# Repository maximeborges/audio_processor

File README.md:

# Audio processor

- Symbols: https://github.com/maximeborges/kicad-symbols
- Footprints: https://github.com/maximeborges/kicad-footprints-v4

## Internet sharing to PYNQ via Ethernet

From https://wiki.archlinux.org/index.php/Internet_sharing

### On the PYNQ:
  
    ip route add default via 192.168.2.1 dev eth0

Where `192.168.2.1` is the computer sharing the connexion.

### On the other computer:

Replace `net0` with local network and `internet0` with external network. For example `net0`->`enp9s0` and `internet0`->`wlp8s0`.

    sysctl net.ipv4.ip_forward=1
    iptables -t nat -A POSTROUTING -o internet0 -j MASQUERADE
    iptables -A FORWARD -m conntrack --ctstate RELATED,ESTABLISHED -j ACCEPT
    iptables -A FORWARD -i net0 -o internet0 -j ACCEPT

### DNS resolution:
Add to /etc/resolv.conf:

    nameserver 185.121.177.177
    nameserver 185.121.177.53

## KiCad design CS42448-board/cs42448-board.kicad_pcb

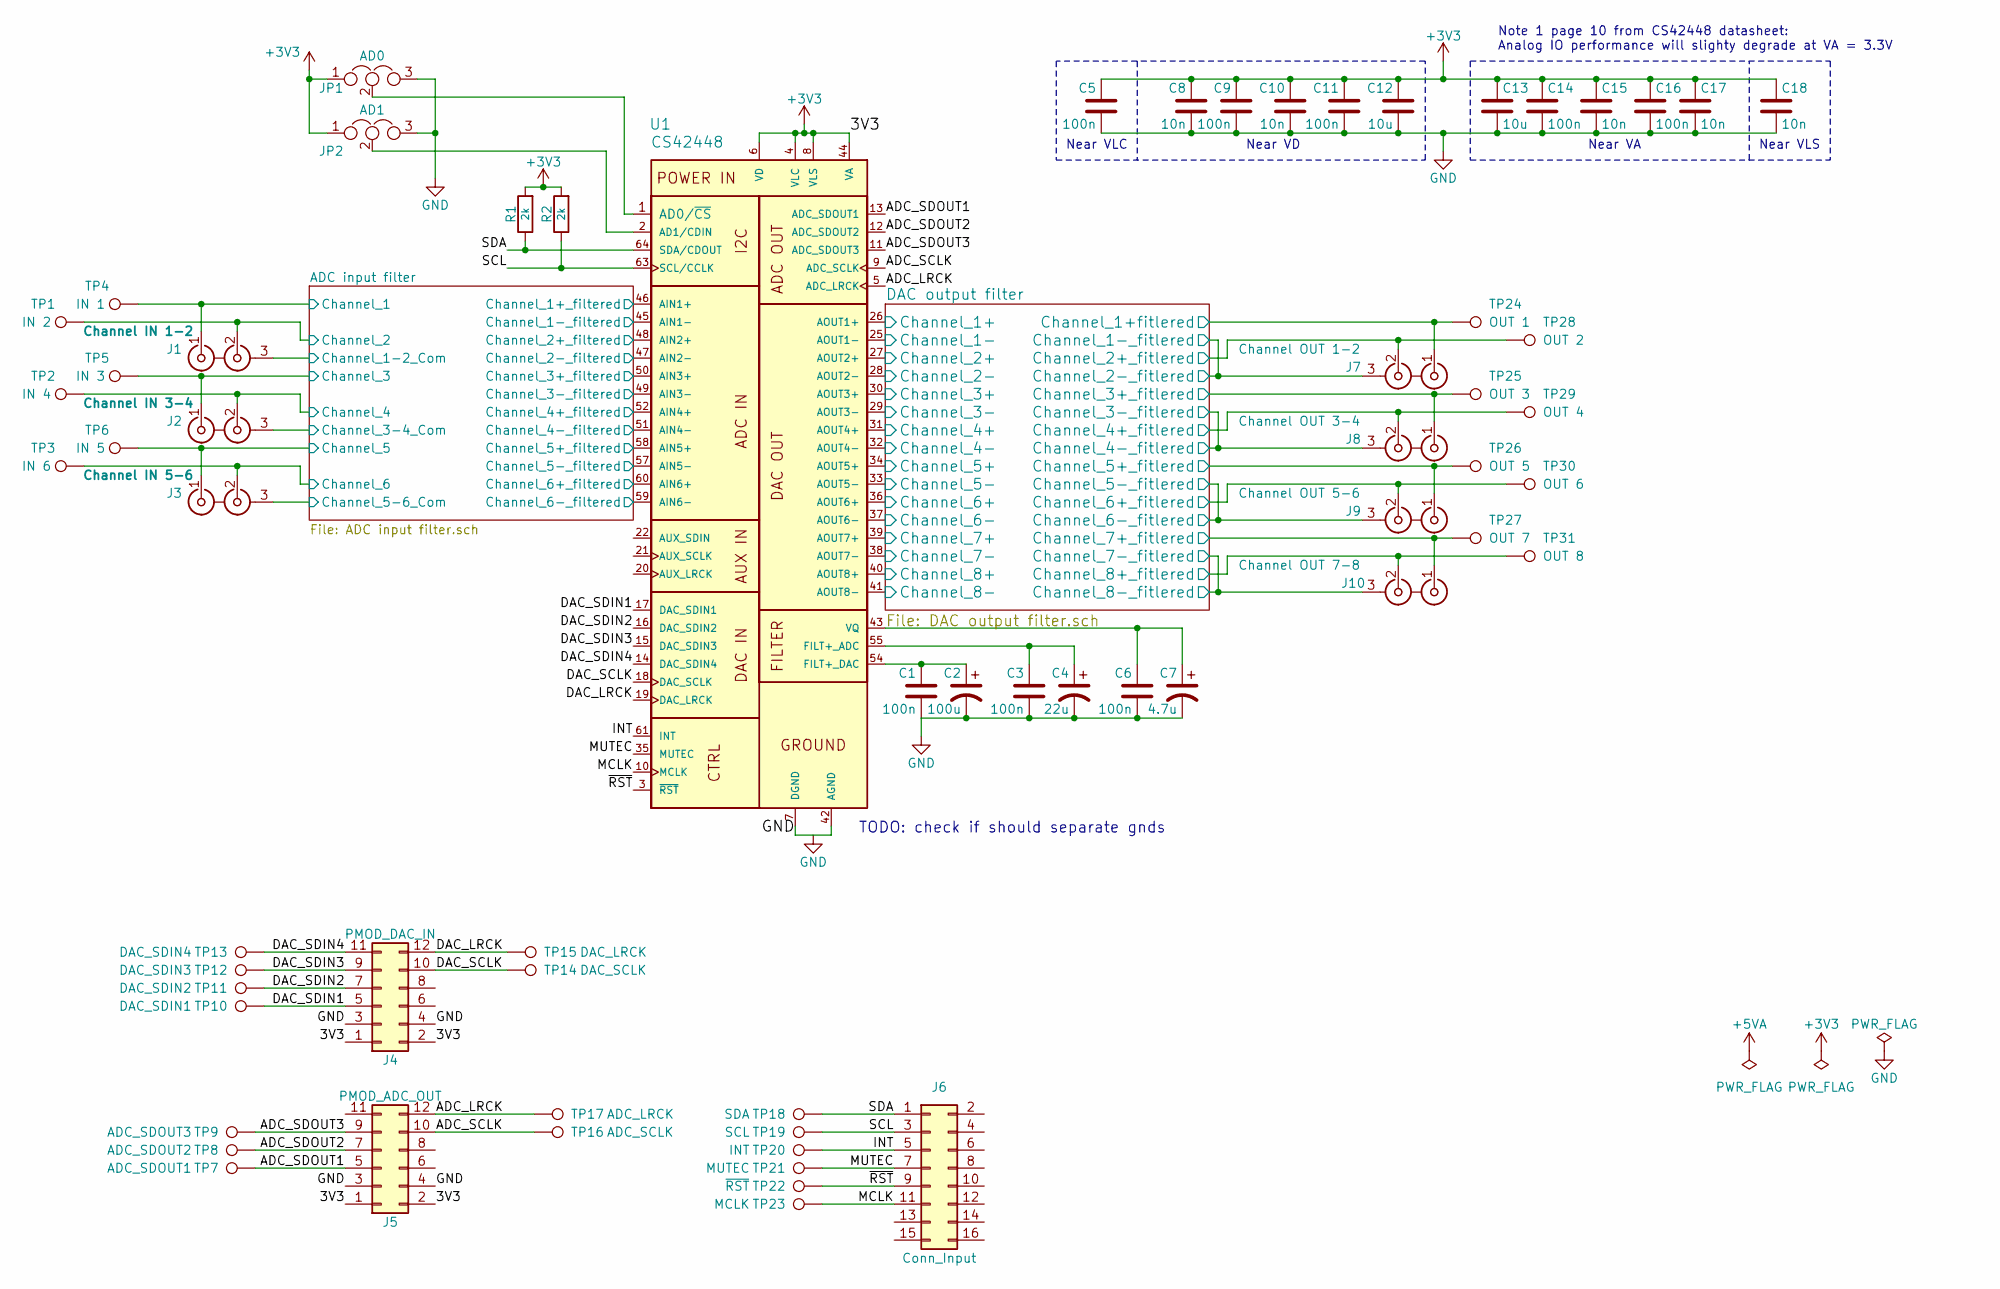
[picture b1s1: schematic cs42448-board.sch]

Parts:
C1, C3, C5, C6, C9, C11, C14, C16: 100n; C_1206_HandSoldering
C2: 100u; CP_Radial_D5.0mm_P2.00mm
C4: 22u; CP_Radial_D5.0mm_P2.00mm
C7: 4.7u; CP_Radial_D5.0mm_P2.00mm
C8, C10, C15, C17, C18: 10n; C_1206_HandSoldering
C12, C13: 10u; C_1206_HandSoldering
J1: Channel IN 1-2; PJRAS1X2S01AUX
J2: Channel IN 3-4; PJRAS1X2S01AUX
J3: Channel IN 5-6; PJRAS1X2S01AUX
J4: PMOD_DAC_IN; PinHeader_2x06_P2.54mm_Horizontal
J5: PMOD_ADC_OUT; PinHeader_2x06_P2.54mm_Horizontal
J6: Conn_Input; Pin_Header_Straight_2x08_Pitch2.54mm
J7: Channel OUT 1-2; PJRAS1X2S01AUX
J8: Channel OUT 3-4; PJRAS1X2S01AUX
J9: Channel OUT 5-6; PJRAS1X2S01AUX
J10: Channel OUT 7-8; PJRAS1X2S01AUX
JP1: AD0; SolderJumper-3_P1.3mm_Open_Pad1.0x1.5mm
JP2: AD1; SolderJumper-3_P1.3mm_Open_Pad1.0x1.5mm
R1, R2: 2k; R_1206_HandSoldering
TP1: IN 2; PINTST
TP2: IN 4; PINTST
TP3: IN 6; PINTST
TP4: IN 1; PINTST
TP5: IN 3; PINTST
TP6: IN 5; PINTST
TP7: ADC_SDOUT1; PINTST
TP8: ADC_SDOUT2; PINTST
TP9: ADC_SDOUT3; PINTST
TP10: DAC_SDIN1; PINTST
TP11: DAC_SDIN2; PINTST
TP12: DAC_SDIN3; PINTST
TP13: DAC_SDIN4; PINTST
TP14: DAC_SCLK; PINTST
TP15: DAC_LRCK; PINTST
TP16: ADC_SCLK; PINTST
TP17: ADC_LRCK; PINTST
TP18: SDA; PINTST
TP19: SCL; PINTST
TP20: INT; PINTST
TP21: MUTEC; PINTST
TP22: ~RST; PINTST
TP23: MCLK; PINTST
TP24: OUT 1; PINTST
TP25: OUT 3; PINTST
TP26: OUT 5; PINTST
TP27: OUT 7; PINTST
TP28: OUT 2; PINTST
TP29: OUT 4; PINTST
TP30: OUT 6; PINTST
TP31: OUT 8; PINTST
U1: CS42448; LQFP-64_10x10mm_P0.5mm

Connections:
+3V3: C5.1, C8.1, C9.1, C10.1, C11.1, C12.1, C13.1, C14.1, C15.1, C16.1, C17.1, C18.1, J4.1, J4.2, J5.1, J5.2, JP1.1, JP2.1, R1.2, R2.2, U1.4 (VLC), U1.6 (VD), U1.8 (VLS), U1.24 (VD), U1.44 (VA), U1.53 (VA)
/ADC input filter/Channel_1: J1.1 (IN1), TP4.1; also elsewhere on the board
/ADC input filter/Channel_1+_filtered: U1.46 (AIN1+); also elsewhere on the board
/ADC input filter/Channel_1-2_Com: J1.3 (EXT); also elsewhere on the board
/ADC input filter/Channel_1-_filtered: U1.45 (AIN1-); also elsewhere on the board
/ADC input filter/Channel_2: J1.2 (IN2), TP1.1; also elsewhere on the board
/ADC input filter/Channel_2+_filtered: U1.48 (AIN2+); also elsewhere on the board
/ADC input filter/Channel_2-_filtered: U1.47 (AIN2-); also elsewhere on the board
/ADC input filter/Channel_3: J2.1 (IN1), TP5.1; also elsewhere on the board
/ADC input filter/Channel_3+_filtered: U1.50 (AIN3+); also elsewhere on the board
/ADC input filter/Channel_3-4_Com: J2.3 (EXT); also elsewhere on the board
/ADC input filter/Channel_3-_filtered: U1.49 (AIN3-); also elsewhere on the board
/ADC input filter/Channel_4: J2.2 (IN2), TP2.1; also elsewhere on the board
/ADC input filter/Channel_4+_filtered: U1.52 (AIN4+); also elsewhere on the board
/ADC input filter/Channel_4-_filtered: U1.51 (AIN4-); also elsewhere on the board
/ADC input filter/Channel_5: J3.1 (IN1), TP6.1; also elsewhere on the board
/ADC input filter/Channel_5+_filtered: U1.58 (AIN5+); also elsewhere on the board
/ADC input filter/Channel_5-6_Com: J3.3 (EXT); also elsewhere on the board
/ADC input filter/Channel_5-_filtered: U1.57 (AIN5-); also elsewhere on the board
/ADC input filter/Channel_6: J3.2 (IN2), TP3.1; also elsewhere on the board
/ADC input filter/Channel_6+_filtered: U1.60 (AIN6+); also elsewhere on the board
/ADC input filter/Channel_6-_filtered: U1.59 (AIN6-); also elsewhere on the board
/ADC_LRCK: J5.12, TP17.1, U1.5 (ADC_LRCK)
/ADC_SCLK: J5.10, TP16.1, U1.9 (ADC_SCLK)
/ADC_SDOUT1: J5.5, TP7.1, U1.13 (ADC_SDOUT1)
/ADC_SDOUT2: J5.7, TP8.1, U1.12 (ADC_SDOUT2)
/ADC_SDOUT3: J5.9, TP9.1, U1.11 (ADC_SDOUT3)
/DAC output filter/Channel_1+: U1.26 (AOUT1+); also elsewhere on the board
/DAC output filter/Channel_1+fitlered: J7.1 (IN1), TP24.1; also elsewhere on the board
/DAC output filter/Channel_1-: J7.3 (EXT), U1.25 (AOUT1-), U1.28 (AOUT2-)
/DAC output filter/Channel_2+: U1.27 (AOUT2+); also elsewhere on the board
/DAC output filter/Channel_2+_fitlered: J7.2 (IN2), TP28.1; also elsewhere on the board
/DAC output filter/Channel_3+: U1.30 (AOUT3+); also elsewhere on the board
/DAC output filter/Channel_3+_fitlered: J8.1 (IN1), TP25.1; also elsewhere on the board
/DAC output filter/Channel_3-: J8.3 (EXT), U1.29 (AOUT3-), U1.32 (AOUT4-)
/DAC output filter/Channel_4+: U1.31 (AOUT4+); also elsewhere on the board
/DAC output filter/Channel_4+_fitlered: J8.2 (IN2), TP29.1; also elsewhere on the board
/DAC output filter/Channel_5+: U1.34 (AOUT5+); also elsewhere on the board
/DAC output filter/Channel_5+_fitlered: J9.1 (IN1), TP26.1; also elsewhere on the board
/DAC output filter/Channel_5-: J9.3 (EXT), U1.33 (AOUT5-), U1.37 (AOUT6-)
/DAC output filter/Channel_6+: U1.36 (AOUT6+); also elsewhere on the board
/DAC output filter/Channel_6+_fitlered: J9.2 (IN2), TP30.1; also elsewhere on the board
/DAC output filter/Channel_7+: U1.39 (AOUT7+); also elsewhere on the board
/DAC output filter/Channel_7+_fitlered: J10.1 (IN1), TP27.1; also elsewhere on the board
/DAC output filter/Channel_7-: J10.3 (EXT), U1.38 (AOUT7-), U1.41 (AOUT8-)
/DAC output filter/Channel_8+: U1.40 (AOUT8+); also elsewhere on the board
/DAC output filter/Channel_8+_fitlered: J10.2 (IN2), TP31.1; also elsewhere on the board
/DAC_LRCK: J4.12, TP15.1, U1.19 (DAC_LRCK)
/DAC_SCLK: J4.10, TP14.1, U1.18 (DAC_SCLK)
/DAC_SDIN1: J4.5, TP10.1, U1.17 (DAC_SDIN1)
/DAC_SDIN2: J4.7, TP11.1, U1.16 (DAC_SDIN2)
/DAC_SDIN3: J4.9, TP12.1, U1.15 (DAC_SDIN3)
/DAC_SDIN4: J4.11, TP13.1, U1.14 (DAC_SDIN4)
/INT: J6.5, TP20.1, U1.61 (INT)
/MCLK: J6.11, TP23.1, U1.10 (MCLK)
/MUTEC: J6.7, TP21.1, U1.35 (MUTEC)
/SCL: J6.3, R2.1, TP19.1, U1.63 (SCL/CCLK)
/SDA: J6.1, R1.1, TP18.1, U1.64 (SDA/CDOUT)
/~RST: J6.9, TP22.1, U1.3 (~RST)
GND: C1.2, C2.2, C3.2, C4.2, C5.2, C6.2, C7.2, C8.2, C9.2, C10.2, C11.2, C12.2, C13.2, C14.2, C15.2, C16.2, C17.2, C18.2, J4.3, J4.4, J5.3, J5.4, JP1.3, JP2.3, U1.7 (DGND), U1.23 (DGND), U1.42 (AGND), U1.56 (AGND), U1.62 (DGND); also elsewhere on the board
unnamed: C1.1, C2.1, U1.54 (FILT+_DAC)
unnamed: C3.1, C4.1, U1.55 (FILT+_ADC)
unnamed: C6.1, C7.1, U1.43 (VQ)
unnamed: JP1.2, U1.1 (AD0/~CS)
unnamed: JP2.2, U1.2 (AD1/CDIN)

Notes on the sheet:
Near VA
Near VD
Near VLC
Near VLS
Note 1 page 10 from CS42448 datasheet: Analog IO performance will slighty degrade at VA = 3.3V
TODO: check if should separate gnds

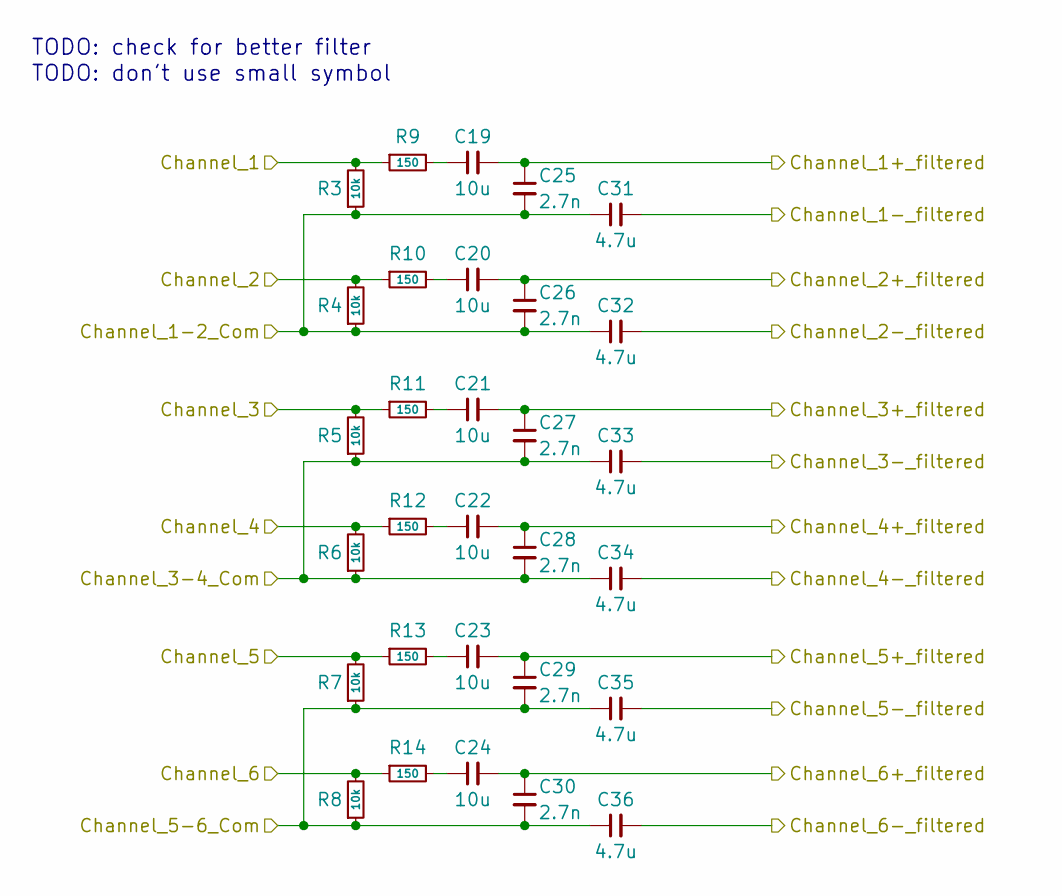
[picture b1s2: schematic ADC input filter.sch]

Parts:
C19, C20, C21, C22, C23, C24: 10u; C_1206_HandSoldering
C25, C26, C27, C28, C29, C30: 2.7n; C_1206_HandSoldering
C31, C32, C33, C34, C35, C36: 4.7u; C_1206_HandSoldering
R3, R4, R5, R6, R7, R8: 10k; R_1206_HandSoldering
R9, R10, R11, R12, R13, R14: 150; R_1206_HandSoldering

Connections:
/ADC input filter/Channel_1: R3.2, R9.1; also elsewhere on the board
/ADC input filter/Channel_1+_filtered: C19.2, C25.1; also elsewhere on the board
/ADC input filter/Channel_1-2_Com: C25.2, C26.2, C31.1, C32.1, R3.1, R4.1; also elsewhere on the board
/ADC input filter/Channel_1-_filtered: C31.2; also elsewhere on the board
/ADC input filter/Channel_2: R4.2, R10.1; also elsewhere on the board
/ADC input filter/Channel_2+_filtered: C20.2, C26.1; also elsewhere on the board
/ADC input filter/Channel_2-_filtered: C32.2; also elsewhere on the board
/ADC input filter/Channel_3: R5.2, R11.1; also elsewhere on the board
/ADC input filter/Channel_3+_filtered: C21.2, C27.1; also elsewhere on the board
/ADC input filter/Channel_3-4_Com: C27.2, C28.2, C33.1, C34.1, R5.1, R6.1; also elsewhere on the board
/ADC input filter/Channel_3-_filtered: C33.2; also elsewhere on the board
/ADC input filter/Channel_4: R6.2, R12.1; also elsewhere on the board
/ADC input filter/Channel_4+_filtered: C22.2, C28.1; also elsewhere on the board
/ADC input filter/Channel_4-_filtered: C34.2; also elsewhere on the board
/ADC input filter/Channel_5: R7.2, R13.1; also elsewhere on the board
/ADC input filter/Channel_5+_filtered: C23.2, C29.1; also elsewhere on the board
/ADC input filter/Channel_5-6_Com: C29.2, C30.2, C35.1, C36.1, R7.1, R8.1; also elsewhere on the board
/ADC input filter/Channel_5-_filtered: C35.2; also elsewhere on the board
/ADC input filter/Channel_6: R8.2, R14.1; also elsewhere on the board
/ADC input filter/Channel_6+_filtered: C24.2, C30.1; also elsewhere on the board
/ADC input filter/Channel_6-_filtered: C36.2; also elsewhere on the board
unnamed: C19.1, R9.2
unnamed: C20.1, R10.2
unnamed: C21.1, R11.2
unnamed: C22.1, R12.2
unnamed: C23.1, R13.2
unnamed: C24.1, R14.2

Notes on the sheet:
TODO: check for better filter
TODO: don't use small symbol

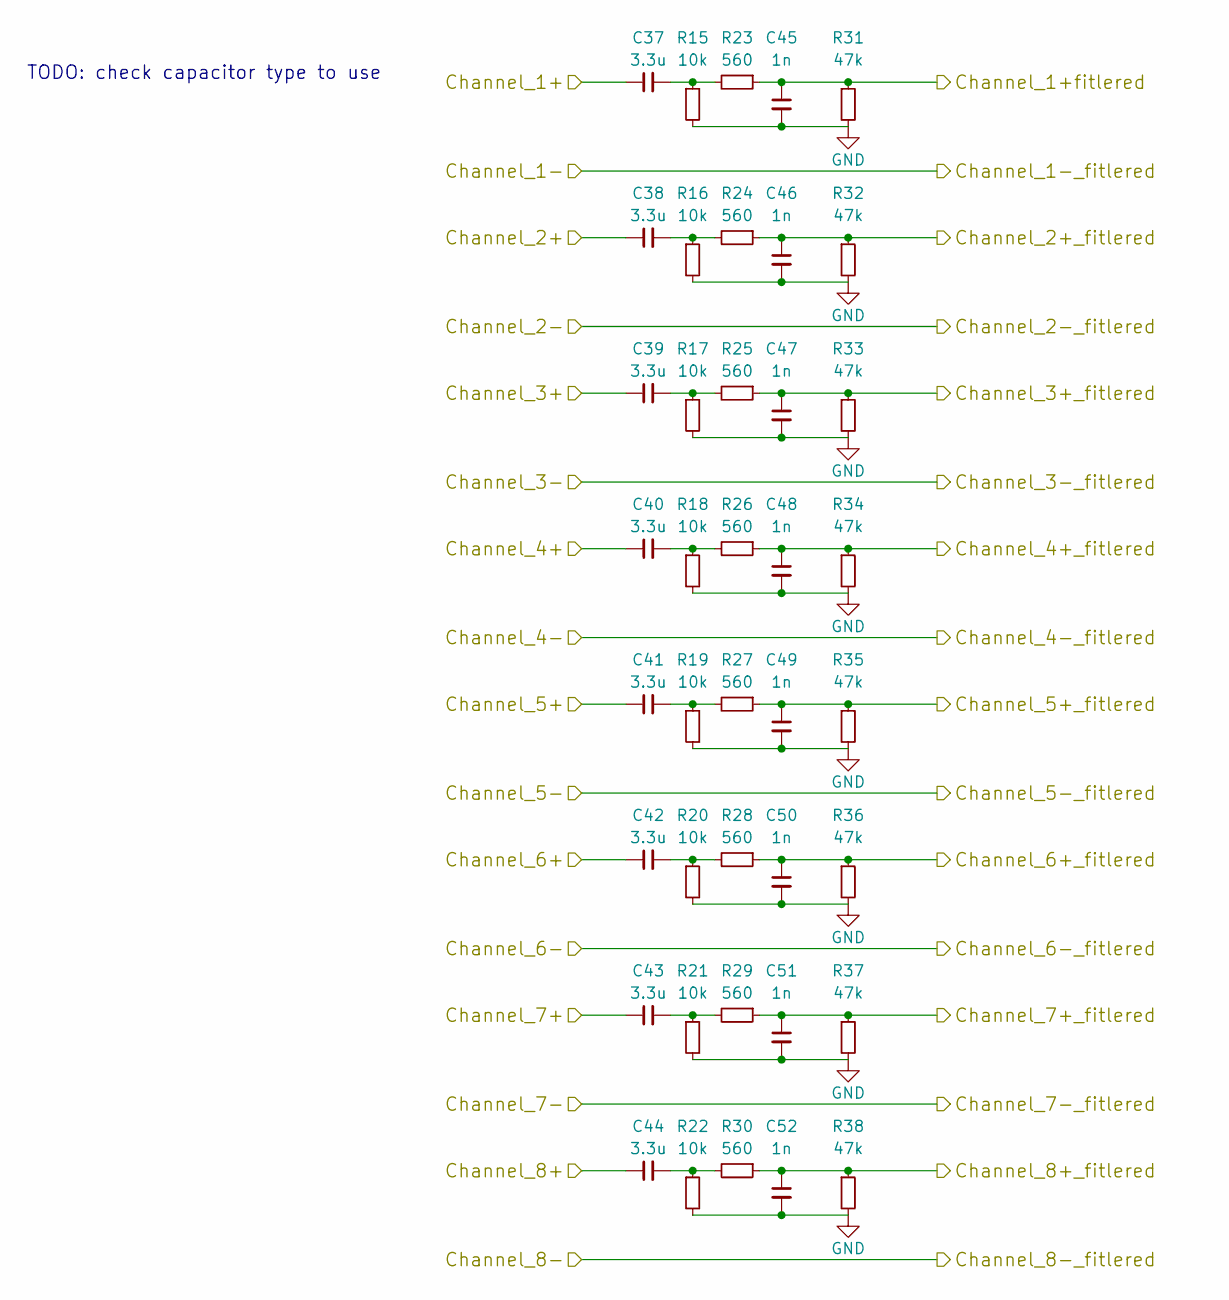
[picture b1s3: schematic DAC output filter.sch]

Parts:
C37, C38, C39, C40, C41, C42, C43, C44: 3.3u; C_1206_HandSoldering
C45, C46, C47, C48, C49, C50, C51, C52: 1n; C_1206_HandSoldering
R15, R16, R17, R18, R19, R20, R21, R22: 10k; R_1206_HandSoldering
R23, R24, R25, R26, R27, R28, R29, R30: 560; R_1206_HandSoldering
R31, R32, R33, R34, R35, R36, R37, R38: 47k; R_1206_HandSoldering

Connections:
/DAC output filter/Channel_1+: C37.1; also elsewhere on the board
/DAC output filter/Channel_1+fitlered: C45.1, R23.1, R31.1; also elsewhere on the board
/DAC output filter/Channel_2+: C38.1; also elsewhere on the board
/DAC output filter/Channel_2+_fitlered: C46.1, R24.1, R32.1; also elsewhere on the board
/DAC output filter/Channel_3+: C39.1; also elsewhere on the board
/DAC output filter/Channel_3+_fitlered: C47.1, R25.1, R33.1; also elsewhere on the board
/DAC output filter/Channel_4+: C40.1; also elsewhere on the board
/DAC output filter/Channel_4+_fitlered: C48.1, R26.1, R34.1; also elsewhere on the board
/DAC output filter/Channel_5+: C41.1; also elsewhere on the board
/DAC output filter/Channel_5+_fitlered: C49.1, R27.1, R35.1; also elsewhere on the board
/DAC output filter/Channel_6+: C42.1; also elsewhere on the board
/DAC output filter/Channel_6+_fitlered: C50.1, R28.1, R36.1; also elsewhere on the board
/DAC output filter/Channel_7+: C43.1; also elsewhere on the board
/DAC output filter/Channel_7+_fitlered: C51.1, R29.1, R37.1; also elsewhere on the board
/DAC output filter/Channel_8+: C44.1; also elsewhere on the board
/DAC output filter/Channel_8+_fitlered: C52.1, R30.1, R38.1; also elsewhere on the board
GND: C45.2, C46.2, C47.2, C48.2, C49.2, C50.2, C51.2, C52.2, R15.2, R16.2, R17.2, R18.2, R19.2, R20.2, R21.2, R22.2, R31.2, R32.2, R33.2, R34.2, R35.2, R36.2, R37.2, R38.2; also elsewhere on the board
unnamed: C37.2, R15.1, R23.2
unnamed: C38.2, R16.1, R24.2
unnamed: C39.2, R17.1, R25.2
unnamed: C40.2, R18.1, R26.2
unnamed: C41.2, R19.1, R27.2
unnamed: C42.2, R20.1, R28.2
unnamed: C43.2, R21.1, R29.2
unnamed: C44.2, R22.1, R30.2

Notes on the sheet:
TODO: check capacitor type to use

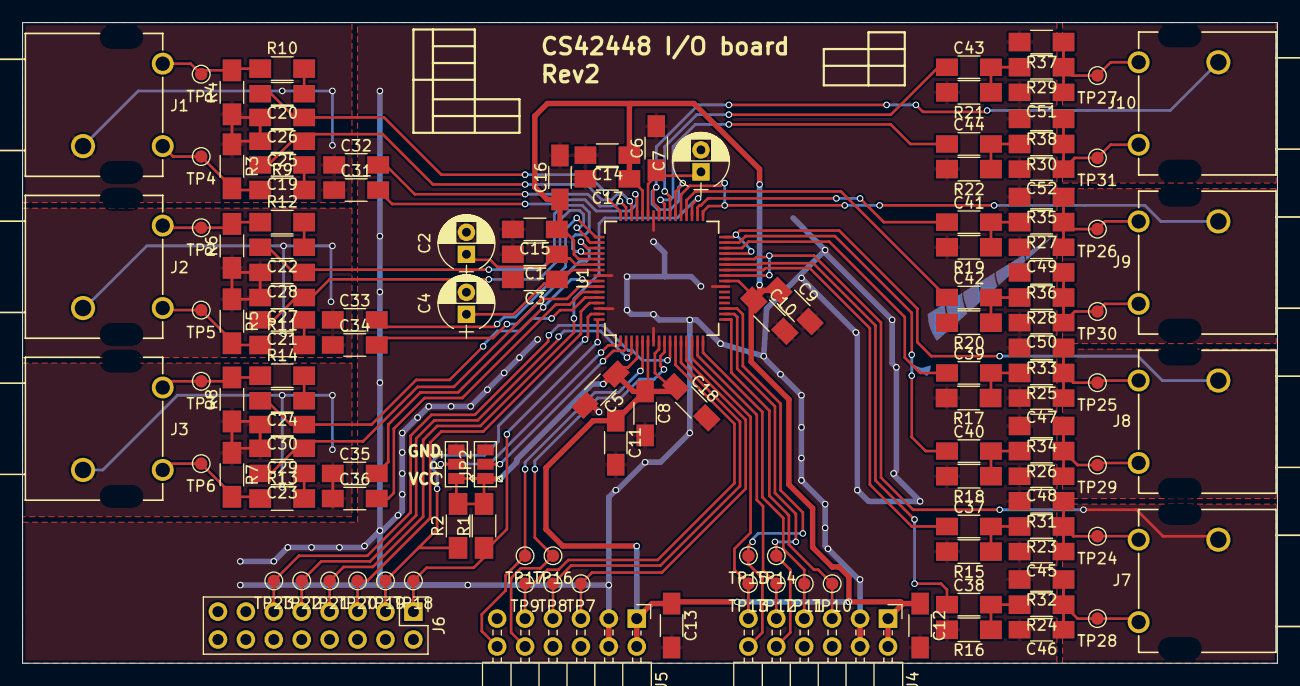
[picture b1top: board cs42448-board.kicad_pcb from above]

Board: 2 copper layers, 114.2 x 58.3 mm, 134 parts (0 on the bottom side), 79 nets.

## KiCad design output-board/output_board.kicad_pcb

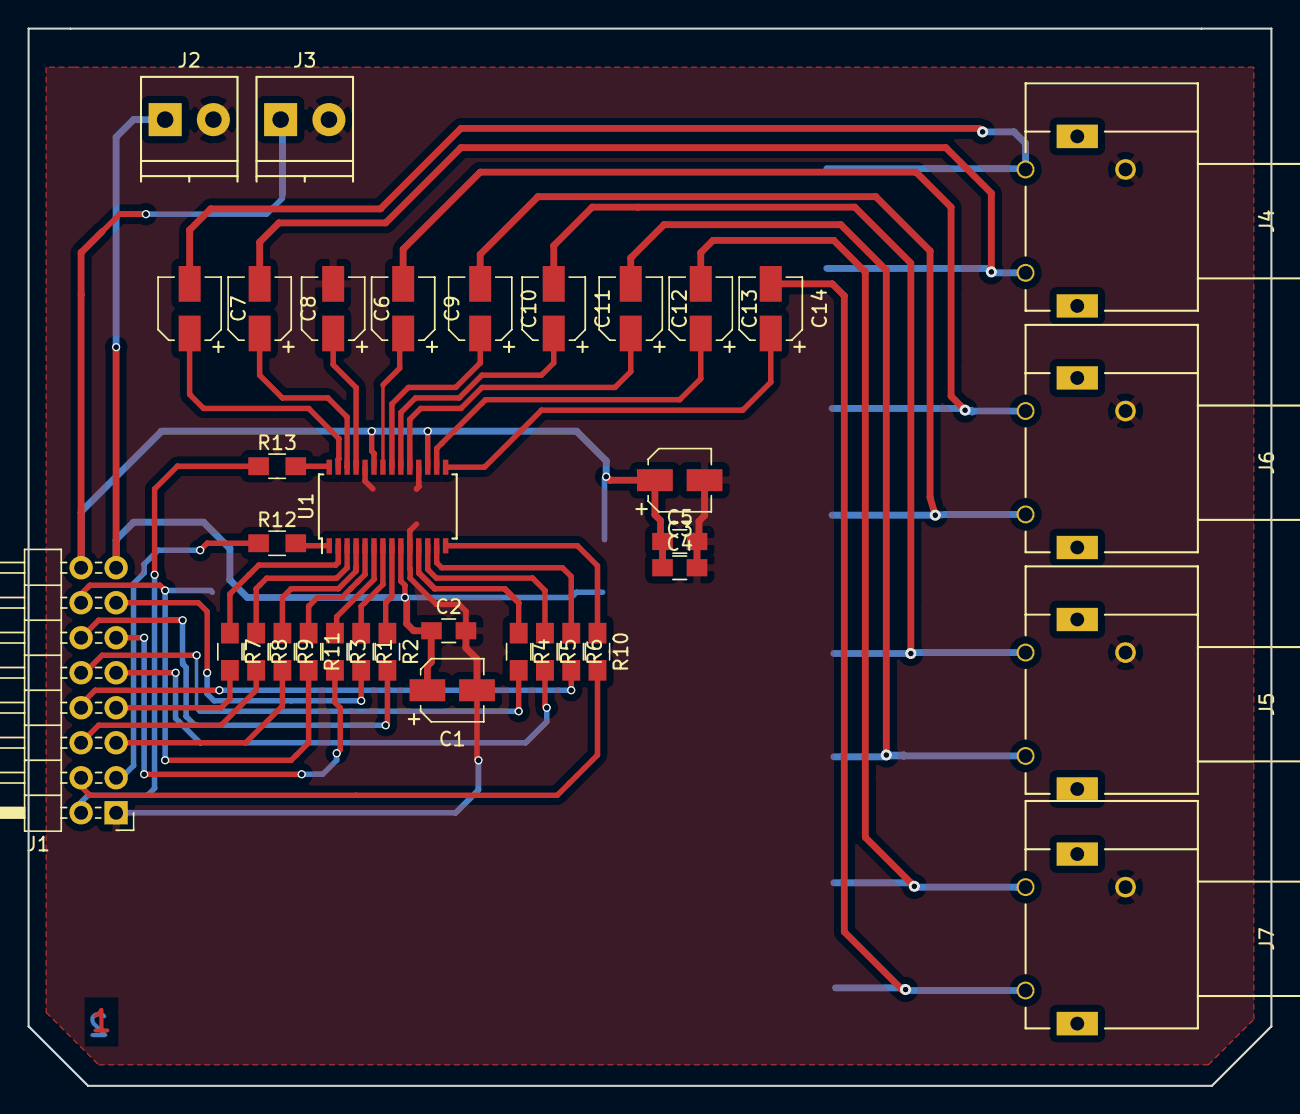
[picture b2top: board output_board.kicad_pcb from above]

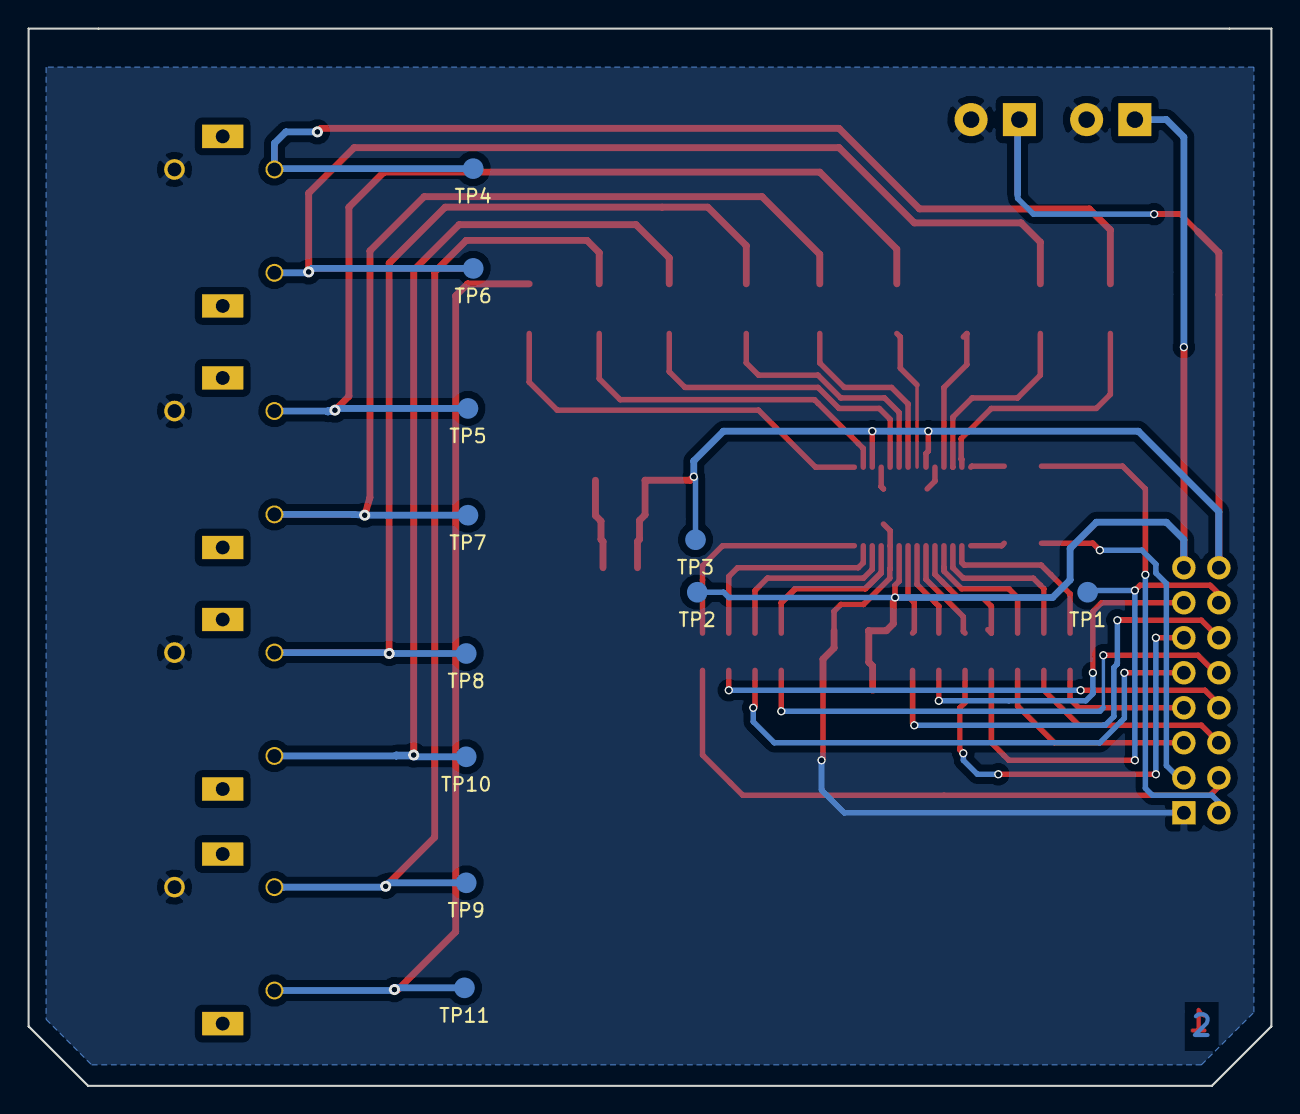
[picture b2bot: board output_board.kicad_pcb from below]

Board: 2 copper layers, 90.2 x 76.7 mm, 46 parts (11 on the bottom side), 46 nets.

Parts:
C1, C3: 10u; CP_Elec_4x5.3
C2, C4, C5: 1u; C_0805_HandSoldering
C6, C7, C8, C9, C10, C11, C12, C13, C14: 10uF; CP_Elec_4x5.3
J1: Conn_Input; Pin_Header_Angled_2x08_Pitch2.54mm
J2: 3V3; TerminalBlock_Pheonix_PT-3.5mm_2pol
J3: 5V; TerminalBlock_Pheonix_PT-3.5mm_2pol
J4: Channel 1-2; PJRAS1X2S01AUX
J5: Channel 5-6; PJRAS1X2S01AUX
J6: Channel 3-4; PJRAS1X2S01AUX
J7: Channel 7-8; PJRAS1X2S01AUX
R1, R2, R3, R4, R5, R6, R7, R8, R9, R10, R11, R12, R13: 100; R_0805_HandSoldering
TP1, TP2, TP3, TP4, TP5, TP6, TP7, TP8, TP9, TP10, TP11: Test_Point; Measurement_Point_Round-SMD-Pad_Small
U1: PCM1681; HTSSOP-28_4.4x9.7mm_Pitch0.65mm_ThermalPad

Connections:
+3V3: C1.1, C2.1, J1.15, J2.1, TP2.1, U1.9
+5VA: C3.1, C4.1, C5.1, J1.16, J3.1, TP3.1, U1.17, U1.23
/BCK: J1.13, R1.2
/DATA1: J1.11, R3.2
/DATA2: J1.10, R4.2
/DATA3: J1.9, R5.2
/DATA4: J1.8, R6.2
/LRCK: J1.12, R2.2
/MC/SEL/DEMP: J1.6, R8.2
/MD/SDA/MUTE: J1.5, R9.2
/MSEL: J1.4, R10.2
/SCK: J1.14, R11.2, TP1.1
/VOUT1: C7.2, J4.1, TP4.1
/VOUT2: C8.2, J4.2, TP6.1
/VOUT3: C9.2, J6.1, TP5.1
/VOUT4: C10.2, J6.2, TP7.1
/VOUT5: C11.2, J5.1, TP8.1
/VOUT6: C12.2, J5.2, TP10.1
/VOUT7: C13.2, J7.1, TP9.1
/VOUT8: C14.2, J7.2, TP11.1
/ZR1/ZR1/FMT0: J1.3, R12.1
/ZR2: J1.2, R13.1
/~MS~/ADR/FMT1: J1.7, R7.2
GNDA: C1.2, C2.2, C3.2, C4.2, C5.2, C6.2, J1.1, J2.2, J3.2, J4.3, J5.3, J6.3, J7.3, U1.10, U1.18, U1.24
unnamed: C6.1, U1.25
unnamed: C7.1, U1.27
unnamed: C8.1, U1.26
unnamed: C9.1, U1.22
unnamed: C10.1, U1.21
unnamed: C11.1, U1.20
unnamed: C12.1, U1.19
unnamed: C13.1, U1.16
unnamed: C14.1, U1.15
unnamed: R1.1, U1.7
unnamed: R2.1, U1.8
unnamed: R3.1, U1.6
unnamed: R4.1, U1.11
unnamed: R5.1, U1.12
unnamed: R6.1, U1.13
unnamed: R7.1, U1.2
unnamed: R8.1, U1.3
unnamed: R9.1, U1.4
unnamed: R10.1, U1.14
unnamed: R11.1, U1.5
unnamed: R12.2, U1.1
unnamed: R13.2, U1.28

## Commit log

2018-01-24 Schematic for output board
2018-03-21 update output-board
2018-04-02 Add graph
2018-04-02 Add instructions to share internet connexion to PYNQ via ethernt
2018-05-07 Add gitignore
2018-05-07 New board with CS42448
2018-05-08 Fix silkscreen
2018-05-25 Update gitignore
2018-05-25 Update to rev2: fix RCA footprint
2018-05-25 [Documentation] Update graph: using I2S and not TDm
2018-05-25 Change logo name in library
